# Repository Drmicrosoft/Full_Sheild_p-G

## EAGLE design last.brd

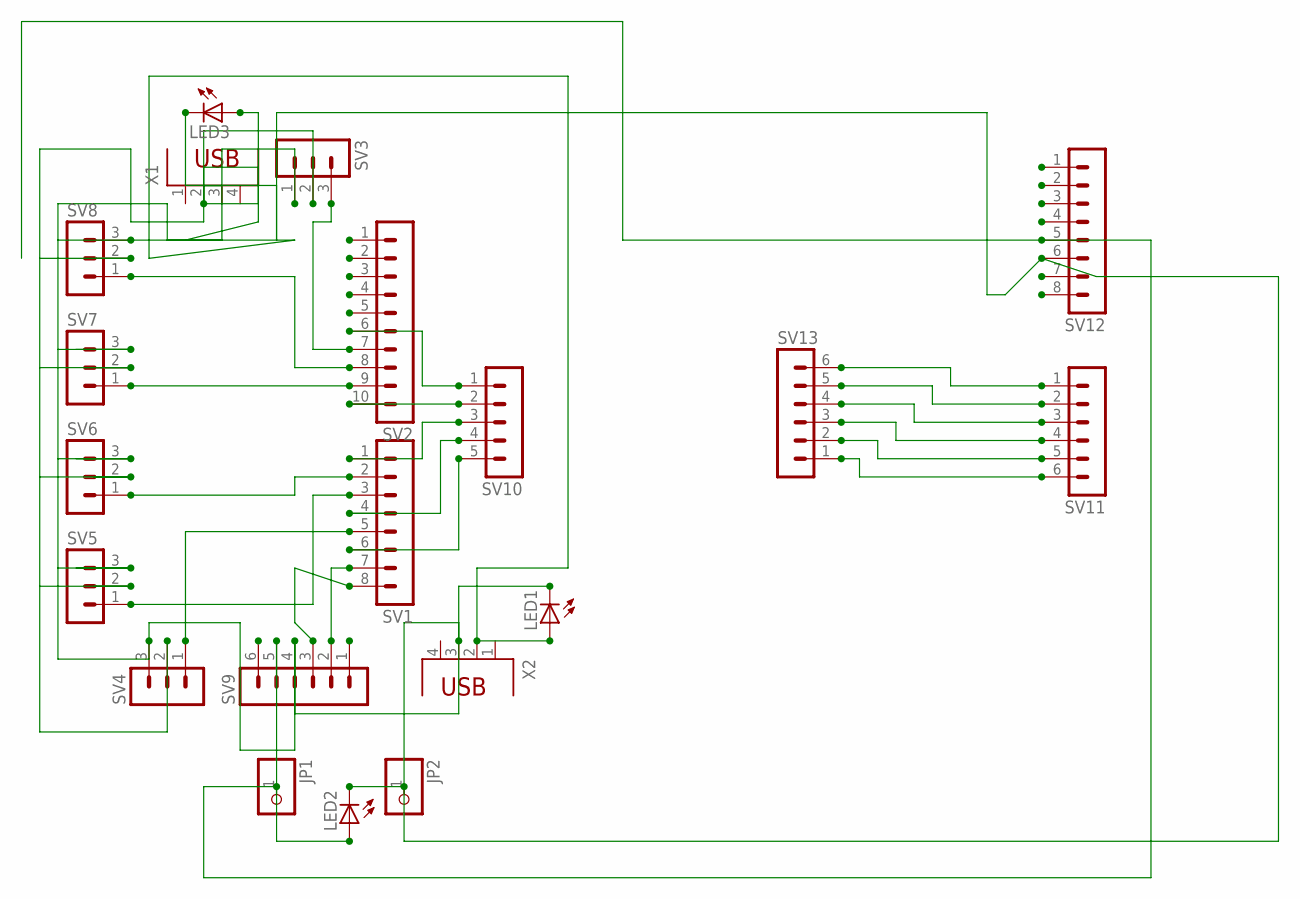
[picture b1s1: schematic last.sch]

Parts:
JP1, JP2: PINHD-1X1; 1X01
LED1, LED2, LED3: LEDLD260; LD260
SV1, SV12: MA08-1
SV2: MA10-1
SV3, SV4, SV5, SV6, SV7, SV8: MA03-1
SV9, SV11, SV13: MA06-1
SV10: MA05-1
X1, X2: PN61729

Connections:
unnamed: SV2.7, SV3.3
unnamed: JP1.1, LED2.A, SV9.5, SV12.5
unnamed: LED1.A, LED3.A, SV3.2, SV4.2, SV5.2, SV6.2, SV7.2, SV8.2, X1.2, X2.2
unnamed: SV2.8, SV8.1
unnamed: SV2.9, SV7.1
unnamed: SV1.2, SV6.1
unnamed: SV11.1, SV13.6
unnamed: SV1.3, SV5.1
unnamed: SV1.5, SV4.1
unnamed: SV11.2, SV13.5
unnamed: SV11.3, SV13.4
unnamed: SV1.8, SV9.3
unnamed: SV1.7, SV9.2
unnamed: SV11.4, SV13.3
unnamed: SV11.5, SV13.2
unnamed: SV11.6, SV13.1
unnamed: SV1.6, SV10.5
unnamed: SV1.4, SV10.4
unnamed: SV1.1, SV10.3
unnamed: SV2.10, SV10.2
unnamed: SV2.6, SV10.1
OMAR: JP2.1, LED1.K (C), LED2.K (C), LED3.K (C), SV3.1, SV4.3, SV5.3, SV6.3, SV7.3, SV8.3, SV9.4, SV12.6, X1.3, X2.3

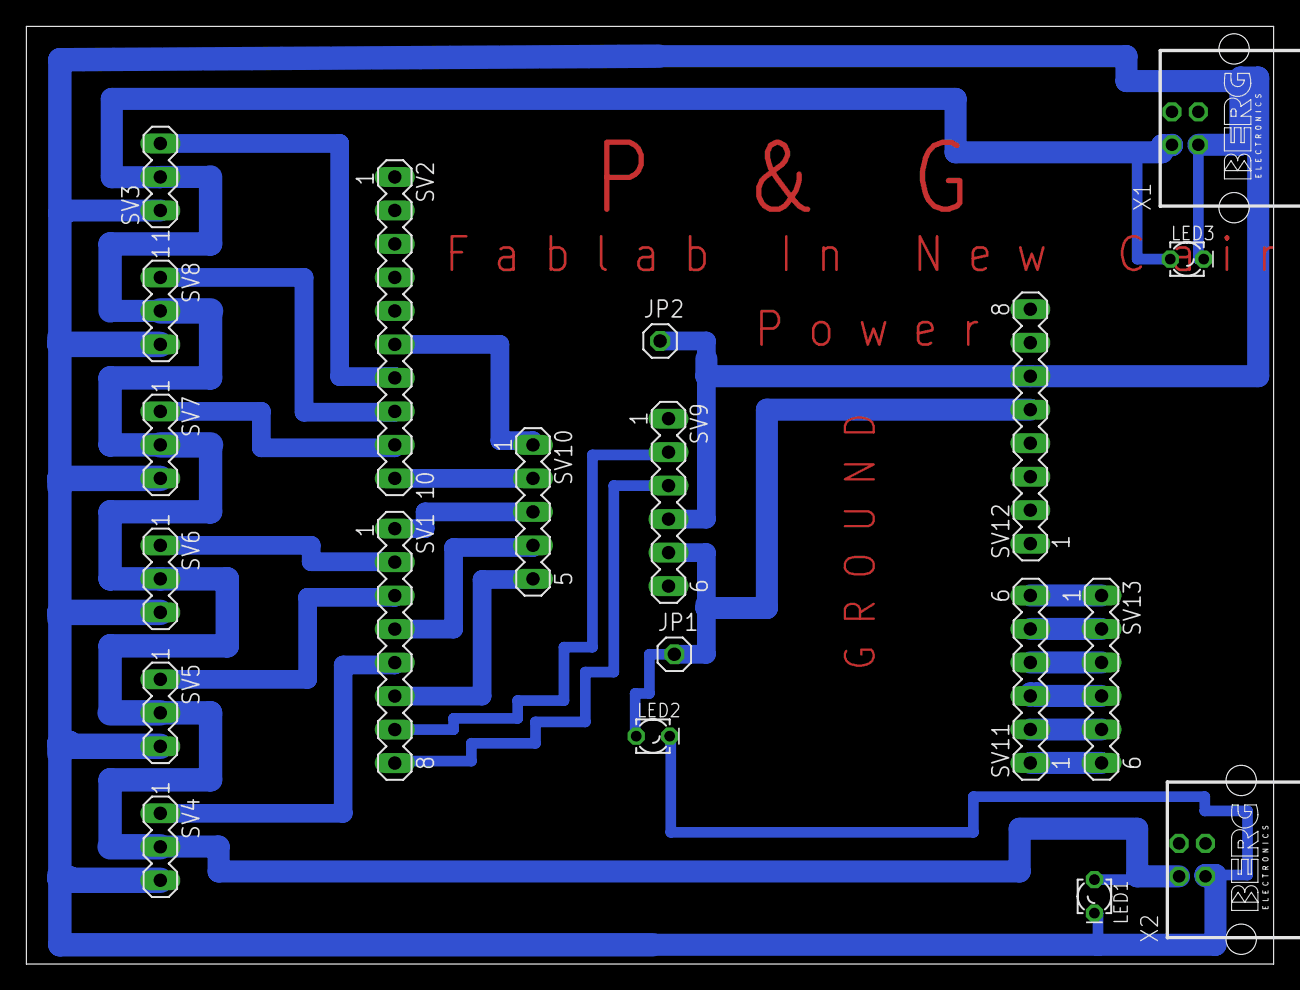
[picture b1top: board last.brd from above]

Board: 2 copper layers, 94.6 x 71.1 mm, 20 parts (0 on the bottom side), 22 nets.
